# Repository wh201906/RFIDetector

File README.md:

# RFIDetector
An opensource hardware project for detecting reader field type(HF/LF)

## Copyright and License
Copyright (c) 2024 wh201906  

All hardware projects in this repository are licensed under [CERN-OHL-S v2](LICENSE.CERN-OHL-S) or any later version.

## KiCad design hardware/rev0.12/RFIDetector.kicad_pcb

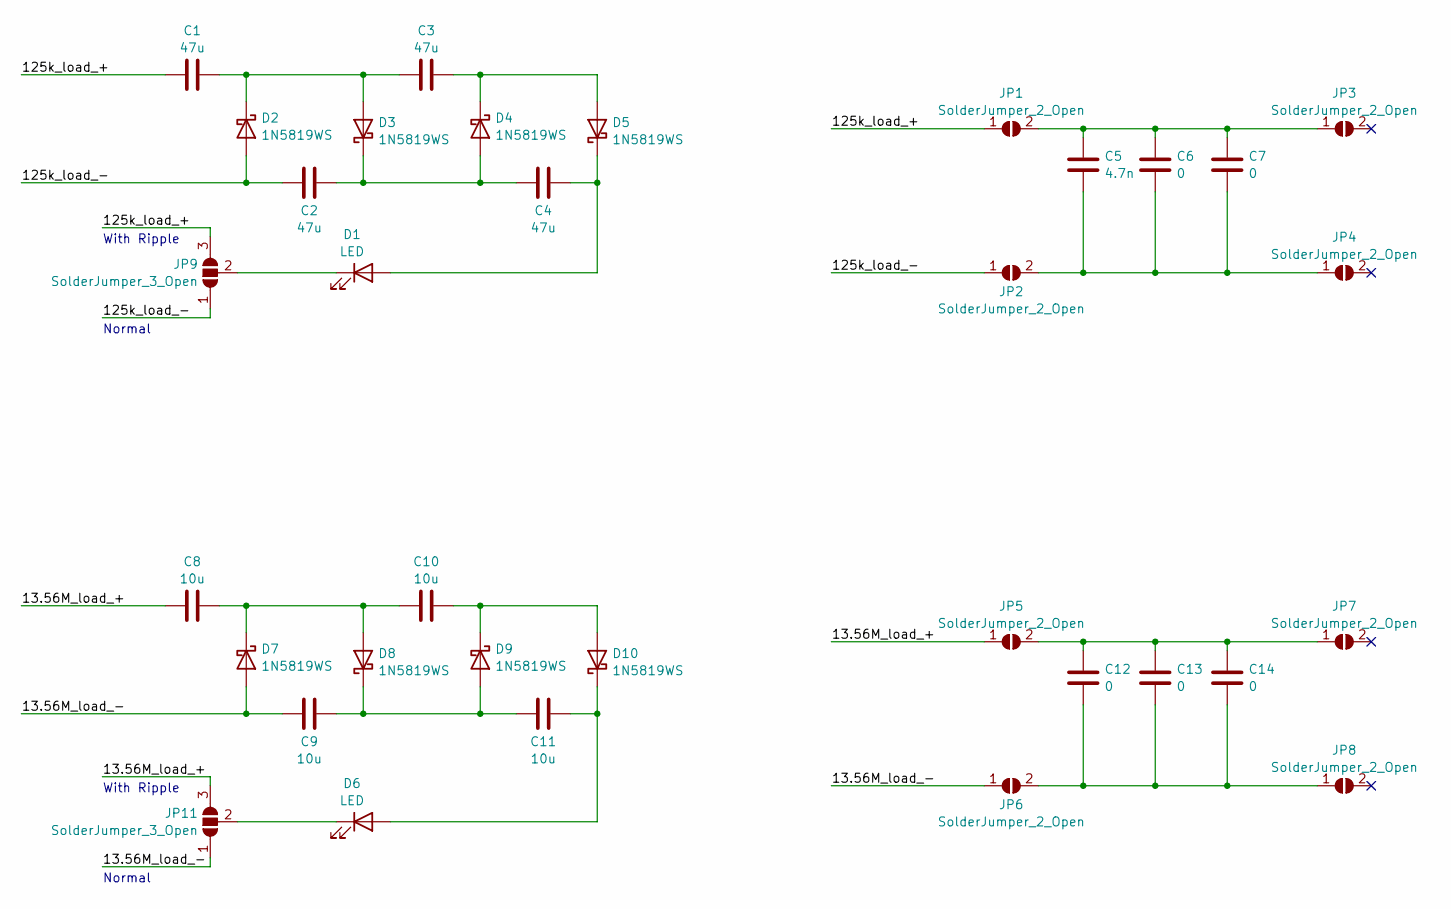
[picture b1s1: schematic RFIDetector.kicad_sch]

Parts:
C1, C2, C3, C4: 47u; C_0603_1608Metric_Pad1.08x0.95mm_HandSolder
C5: 4.7n; C_0603_1608Metric_Pad1.08x0.95mm_HandSolder
C6, C7, C12, C13, C14: 0; C_0603_1608Metric_Pad1.08x0.95mm_HandSolder
C8, C9, C10, C11: 10u; C_0603_1608Metric_Pad1.08x0.95mm_HandSolder
D1, D6: LED; LED_0603_1608Metric_Pad1.05x0.95mm_HandSolder
D2, D3, D4, D5, D7, D8, D9, D10: 1N5819WS; D_SOD-323_HandSoldering
JP1, JP2, JP3, JP4, JP5, JP6, JP7, JP8: SolderJumper_2_Open; SolderJumper-2_P1.3mm_Open_RoundedPad1.0x1.5mm
JP9, JP11: SolderJumper_3_Open; SolderJumper-3_P1.3mm_Open_RoundedPad1.0x1.5mm

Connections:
/13.56M_load_+: C8.1, JP5.1 (A), JP11.3 (B)
/13.56M_load_-: C9.1, D7.2 (A), JP6.1 (A), JP11.1 (A)
/125k_load_+: C1.1, JP1.1 (A), JP9.3 (B)
/125k_load_-: C2.1, D2.2 (A), JP2.1 (A), JP9.1 (A)
unnamed: C4.2, D1.2 (A), D5.1 (K)
unnamed: D1.1 (K), JP9.2 (C)
unnamed: C1.2, C3.1, D2.1 (K), D3.2 (A)
unnamed: C2.2, C4.1, D3.1 (K), D4.2 (A)
unnamed: C3.2, D4.1 (K), D5.2 (A)
unnamed: D6.1 (K), JP11.2 (C)
unnamed: C8.2, C10.1, D7.1 (K), D8.2 (A)
unnamed: C9.2, C11.1, D8.1 (K), D9.2 (A)
unnamed: C10.2, D9.1 (K), D10.2 (A)
unnamed: C11.2, D6.2 (A), D10.1 (K)
unnamed: C5.2, C6.2, C7.2, JP1.2 (B), JP3.1 (A)
unnamed: C5.1, C6.1, C7.1, JP2.2 (B), JP4.1 (A)
unnamed: C12.1, C13.1, C14.1, JP5.2 (B), JP7.1 (A)
unnamed: C12.2, C13.2, C14.2, JP6.2 (B), JP8.1 (A)

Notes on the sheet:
Normal
With Ripple

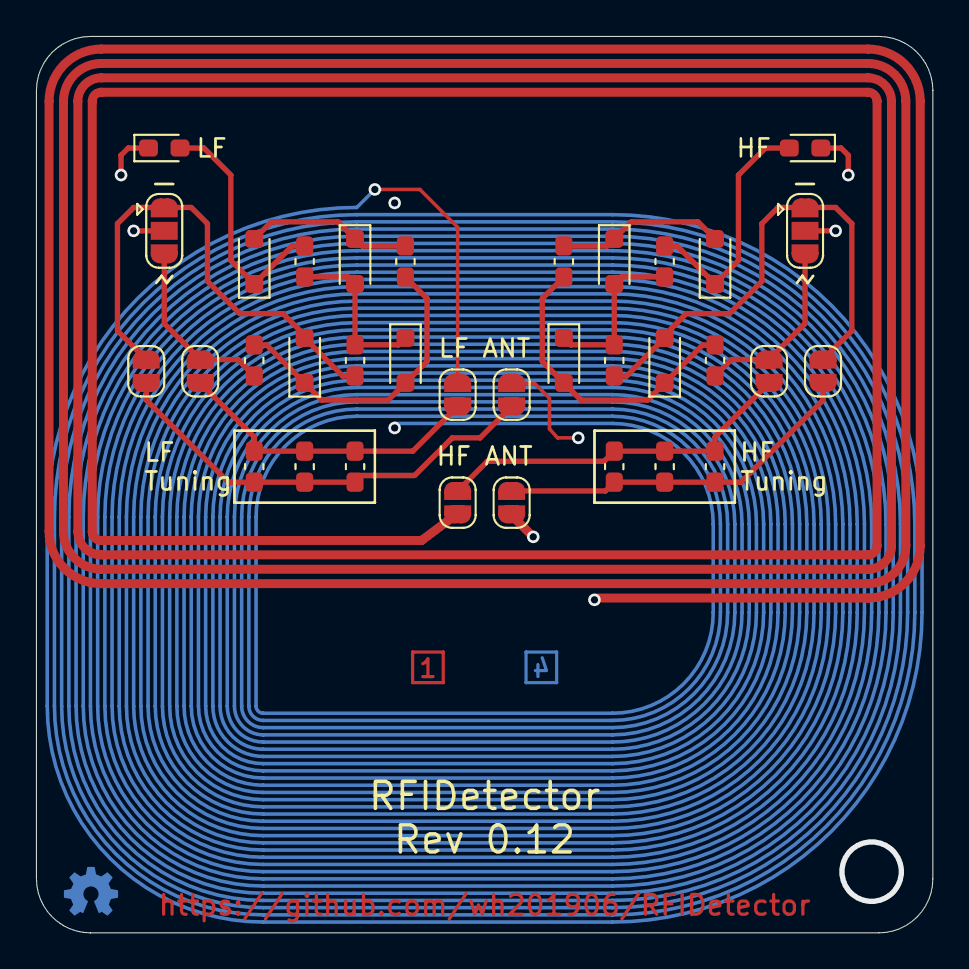
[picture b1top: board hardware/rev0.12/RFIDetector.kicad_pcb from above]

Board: 4 copper layers, 49.8 x 49.8 mm, 34 parts (0 on the bottom side), 18 nets.

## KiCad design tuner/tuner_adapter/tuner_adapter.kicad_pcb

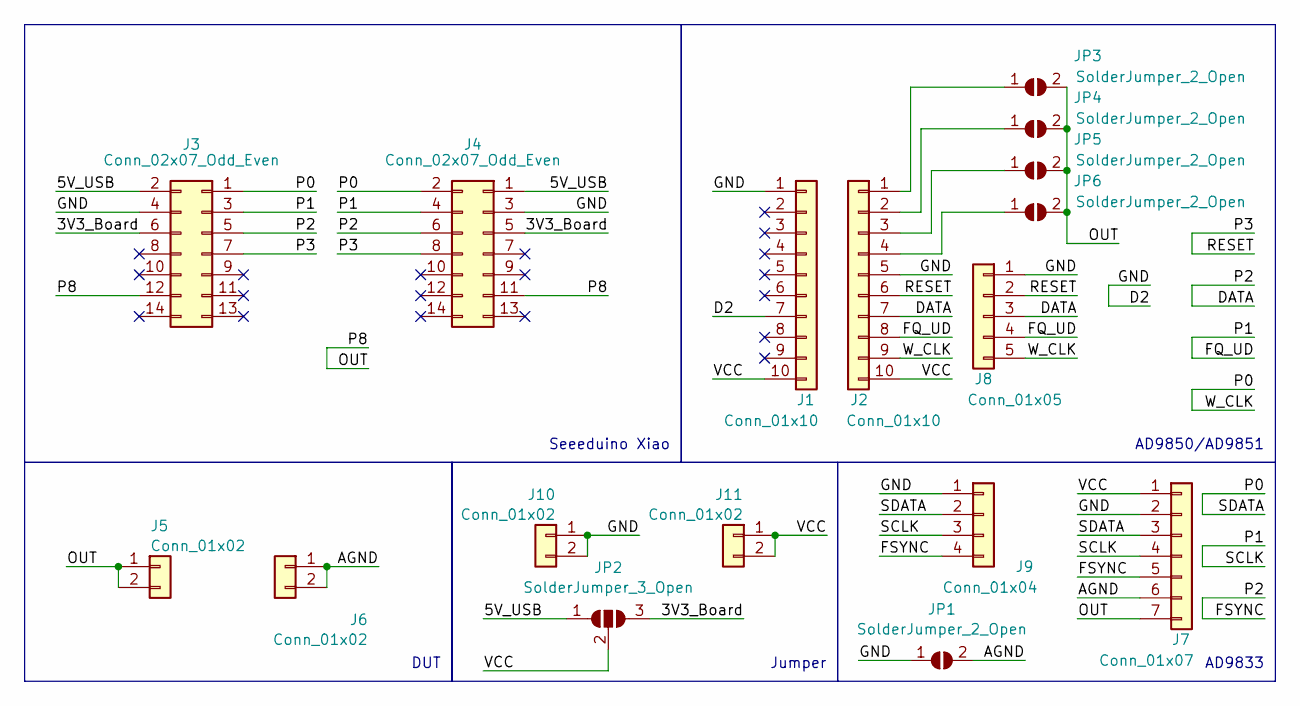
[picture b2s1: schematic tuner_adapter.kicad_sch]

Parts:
J1, J2: Conn_01x10; PinSocket_1x10_P2.54mm_Vertical
J3, J4: Conn_02x07_Odd_Even; PinSocket_2x07_P2.54mm_Vertical
J5, J6: Conn_01x02; PinSocket_1x02_P2.54mm_Vertical
J7: Conn_01x07; PinSocket_1x07_P2.54mm_Vertical
J8: Conn_01x05; PinHeader_1x05_P2.54mm_Vertical
J9: Conn_01x04; PinHeader_1x04_P2.54mm_Vertical
J10, J11: Conn_01x02; PinHeader_1x02_P2.54mm_Vertical
JP1, JP3, JP4, JP5, JP6: SolderJumper_2_Open; SolderJumper-2_P1.3mm_Open_RoundedPad1.0x1.5mm
JP2: SolderJumper_3_Open; SolderJumper-3_P1.3mm_Open_RoundedPad1.0x1.5mm

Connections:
/3V3_Board: J3.6, J4.5, JP2.3 (B)
/5V_USB: J3.2, J4.1, JP2.1 (A)
/AGND: J6.1, J6.2, J7.6, JP1.2 (B)
/D2: J1.1, J1.7, J2.5, J3.4, J4.3, J7.2, J8.1, J9.1, J10.1, J10.2, JP1.1 (A)
/DATA: J2.7, J3.5, J4.6, J7.5, J8.3, J9.4
/FQ_UD: J2.8, J3.3, J4.4, J7.4, J8.4, J9.3
/OUT: J3.12, J4.11, J5.1, J5.2, J7.7, JP3.2 (B), JP4.2 (B), JP5.2 (B), JP6.2 (B)
/P0: J2.9, J3.1, J4.2, J7.3, J8.5, J9.2
/P3: J2.6, J3.7, J4.8, J8.2
/VCC: J1.10, J2.10, J7.1, J11.1, J11.2, JP2.2 (C)
unnamed: J2.1, JP3.1 (A)
unnamed: J2.2, JP4.1 (A)
unnamed: J2.3, JP5.1 (A)
unnamed: J2.4, JP6.1 (A)

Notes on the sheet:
Jumper
AD9833
AD9850/AD9851
DUT
Seeeduino Xiao

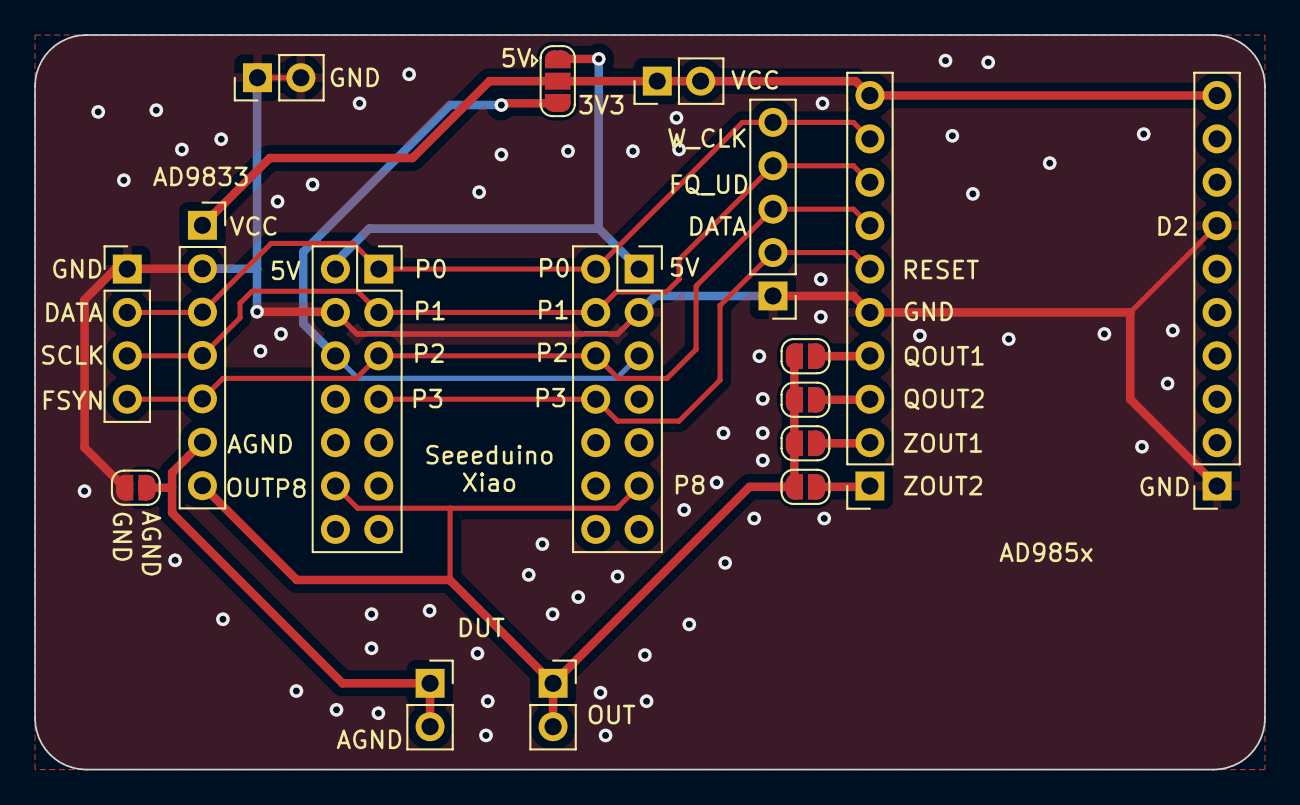
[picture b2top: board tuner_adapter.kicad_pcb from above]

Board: 2 copper layers, 72.0 x 43.0 mm, 17 parts (0 on the bottom side), 14 nets.

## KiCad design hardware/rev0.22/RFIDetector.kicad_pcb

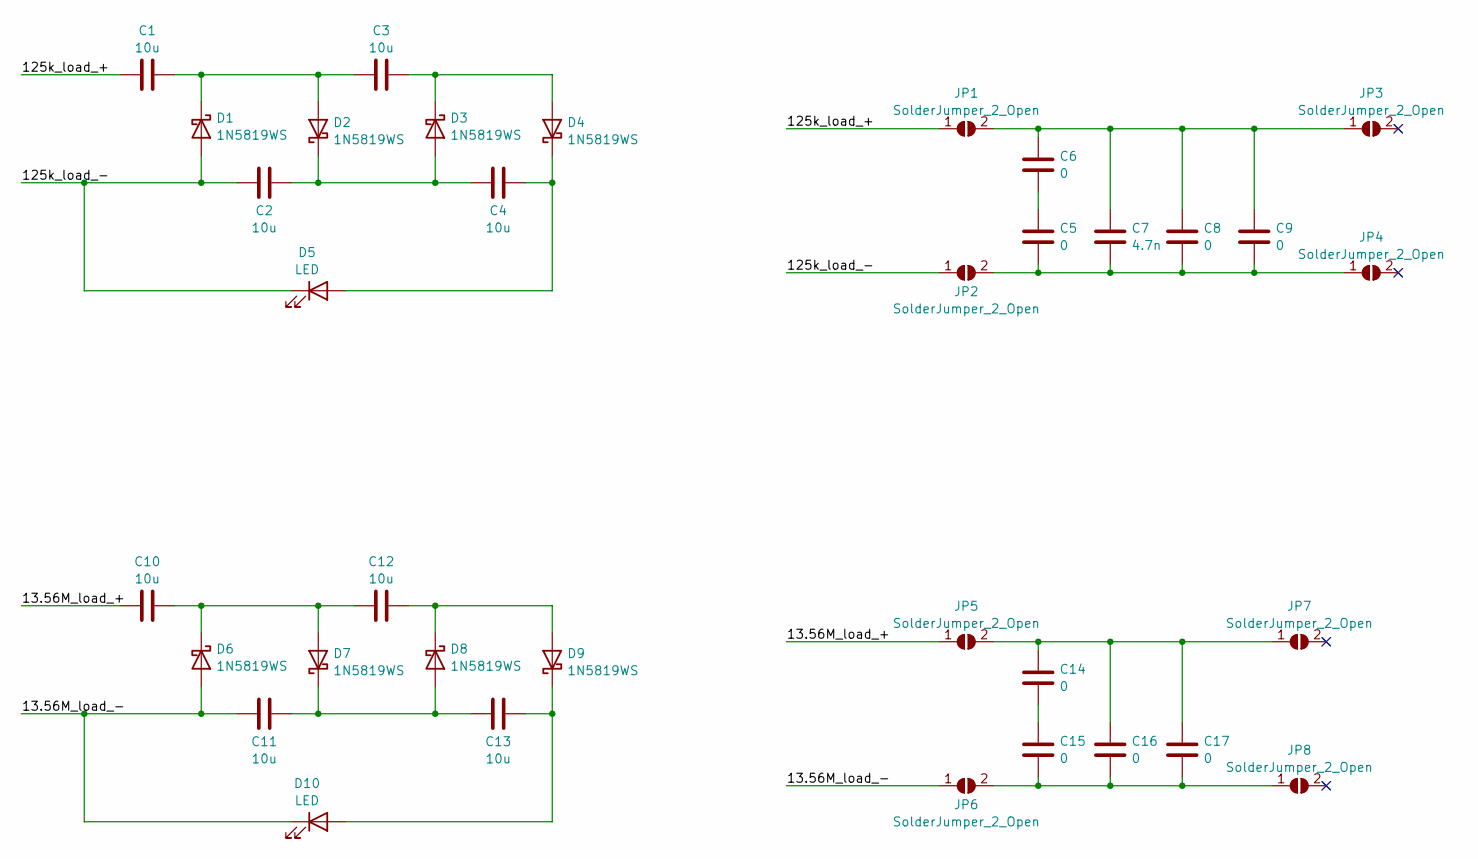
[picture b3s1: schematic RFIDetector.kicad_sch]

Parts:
C1, C2, C3, C4, C10, C11, C12, C13: 10u; C_0603_1608Metric_Pad1.08x0.95mm_HandSolder
C5, C6, C8, C9, C14, C15, C16, C17: 0; C_0603_1608Metric_Pad1.08x0.95mm_HandSolder
C7: 4.7n; C_0603_1608Metric_Pad1.08x0.95mm_HandSolder
D1, D2, D3, D4, D6, D7, D8, D9: 1N5819WS; D_SOD-323_HandSoldering
D5, D10: LED; LED_0603_1608Metric_Pad1.05x0.95mm_HandSolder
JP1, JP2, JP3, JP4, JP5, JP6, JP7, JP8: SolderJumper_2_Open; SolderJumper-2_P1.3mm_Open_RoundedPad1.0x1.5mm

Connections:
/13.56M_load_+: C10.1, JP5.1 (A)
/13.56M_load_-: C11.1, D6.2 (A), D10.1 (K), JP6.1 (A)
/125k_load_+: C1.1, JP1.1 (A)
/125k_load_-: C2.1, D1.2 (A), D5.1 (K), JP2.1 (A)
unnamed: C5.2, C6.1
unnamed: C14.1, C15.1
unnamed: C1.2, C3.1, D1.1 (K), D2.2 (A)
unnamed: C2.2, C4.1, D2.1 (K), D3.2 (A)
unnamed: C3.2, D3.1 (K), D4.2 (A)
unnamed: C4.2, D4.1 (K), D5.2 (A)
unnamed: C10.2, C12.1, D6.1 (K), D7.2 (A)
unnamed: C11.2, C13.1, D7.1 (K), D8.2 (A)
unnamed: C12.2, D8.1 (K), D9.2 (A)
unnamed: C13.2, D9.1 (K), D10.2 (A)
unnamed: C6.2, C7.1, C8.1, C9.1, JP1.2 (B), JP3.1 (A)
unnamed: C5.1, C7.2, C8.2, C9.2, JP2.2 (B), JP4.1 (A)
unnamed: C14.2, C16.2, C17.2, JP5.2 (B), JP7.1 (A)
unnamed: C15.2, C16.1, C17.1, JP6.2 (B), JP8.1 (A)

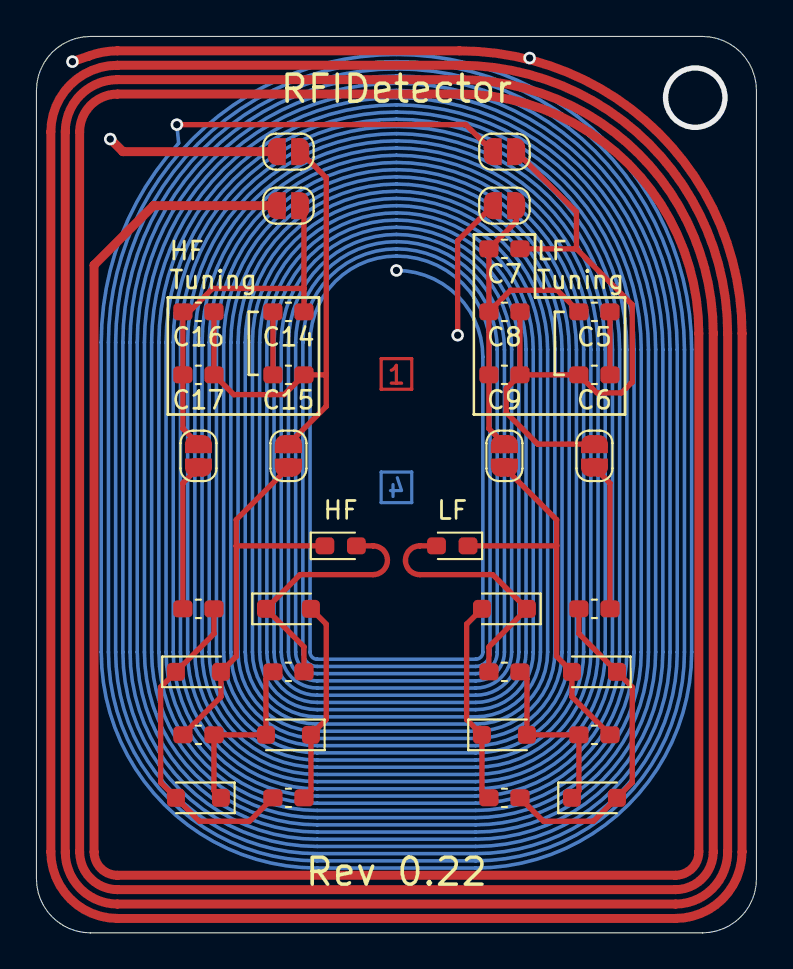
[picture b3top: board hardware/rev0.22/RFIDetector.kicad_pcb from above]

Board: 4 copper layers, 40.0 x 49.8 mm, 35 parts (0 on the bottom side), 18 nets.

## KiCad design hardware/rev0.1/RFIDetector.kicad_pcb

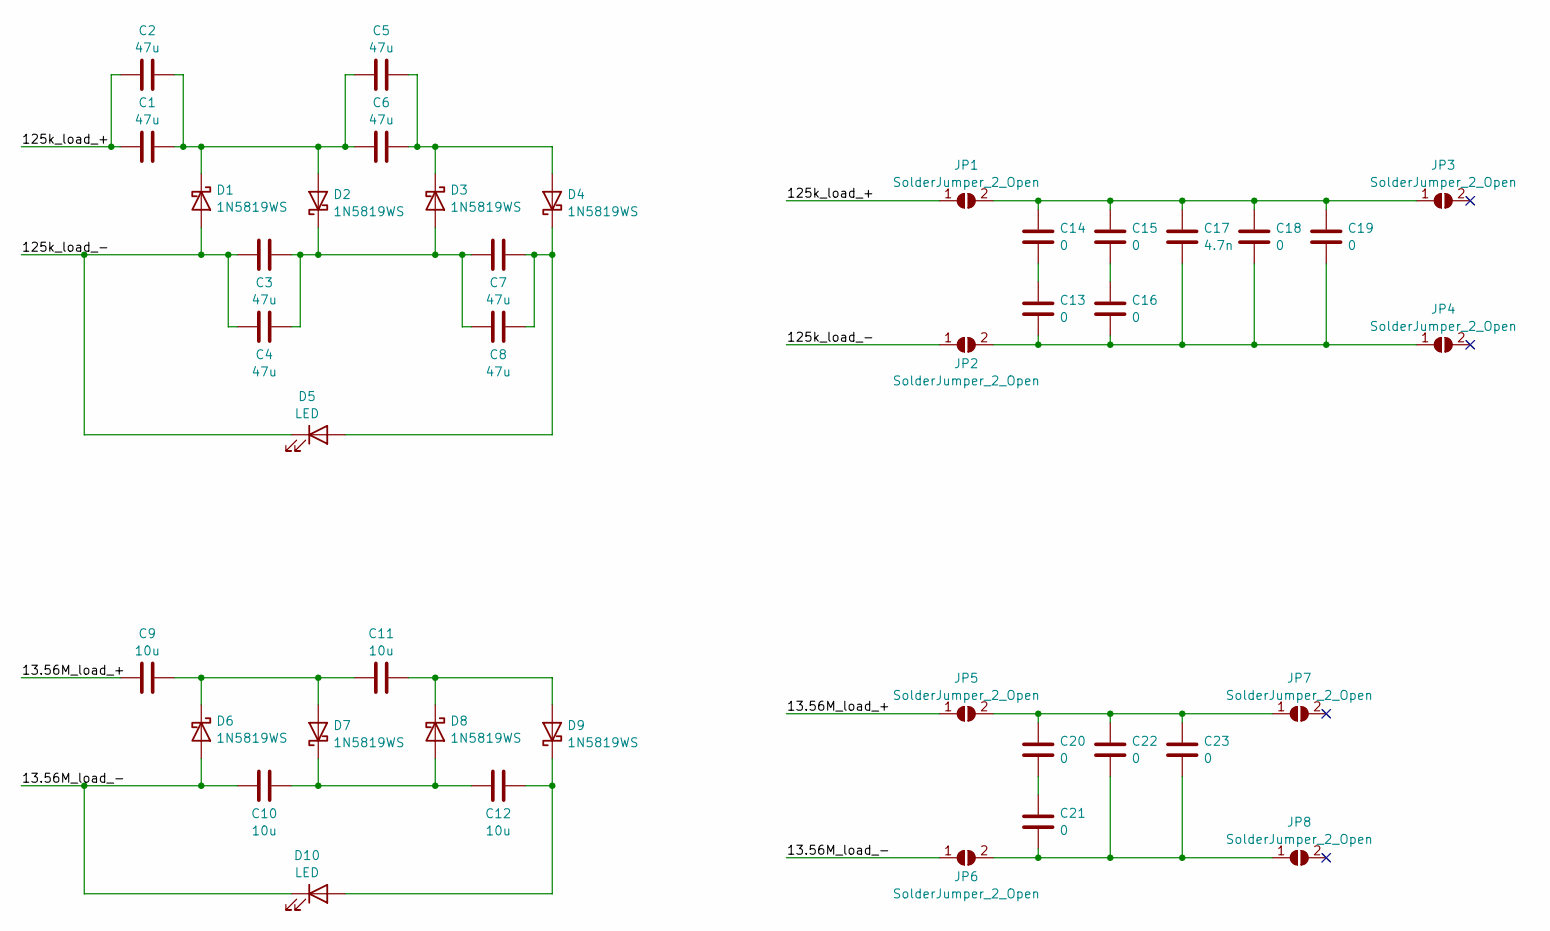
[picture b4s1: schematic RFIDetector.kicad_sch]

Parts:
C1, C2, C3, C4, C5, C6, C7, C8: 47u; C_0603_1608Metric_Pad1.08x0.95mm_HandSolder
C9, C10, C11, C12: 10u; C_0603_1608Metric_Pad1.08x0.95mm_HandSolder
C13, C14, C15, C16, C18, C19, C20, C21, C22, C23: 0; C_0603_1608Metric_Pad1.08x0.95mm_HandSolder
C17: 4.7n; C_0603_1608Metric_Pad1.08x0.95mm_HandSolder
D1, D2, D3, D4, D6, D7, D8, D9: 1N5819WS; D_SOD-323_HandSoldering
D5, D10: LED; LED_0603_1608Metric_Pad1.05x0.95mm_HandSolder
JP1, JP2, JP3, JP4, JP5, JP6, JP7, JP8: SolderJumper_2_Open; SolderJumper-2_P1.3mm_Open_RoundedPad1.0x1.5mm

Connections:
/13.56M_load_+: C9.1, JP5.1 (A)
/13.56M_load_-: C10.1, D6.2 (A), D10.1 (K), JP6.1 (A)
/125k_load_+: C1.1, C2.1, JP1.1 (A)
/125k_load_-: C3.1, C4.1, D1.2 (A), D5.1 (K), JP2.1 (A)
unnamed: C13.1, C14.1
unnamed: C15.2, C16.1
unnamed: C20.1, C21.1
unnamed: C1.2, C2.2, C5.1, C6.1, D1.1 (K), D2.2 (A)
unnamed: C3.2, C4.2, C7.1, C8.1, D2.1 (K), D3.2 (A)
unnamed: C5.2, C6.2, D3.1 (K), D4.2 (A)
unnamed: C7.2, C8.2, D4.1 (K), D5.2 (A)
unnamed: C9.2, C11.1, D6.1 (K), D7.2 (A)
unnamed: C10.2, C12.1, D7.1 (K), D8.2 (A)
unnamed: C11.2, D8.1 (K), D9.2 (A)
unnamed: C12.2, D9.1 (K), D10.2 (A)
unnamed: C14.2, C15.1, C17.2, C18.2, C19.2, JP1.2 (B), JP3.1 (A)
unnamed: C13.2, C16.2, C17.1, C18.1, C19.1, JP2.2 (B), JP4.1 (A)
unnamed: C20.2, C22.1, C23.1, JP5.2 (B), JP7.1 (A)
unnamed: C21.2, C22.2, C23.2, JP6.2 (B), JP8.1 (A)

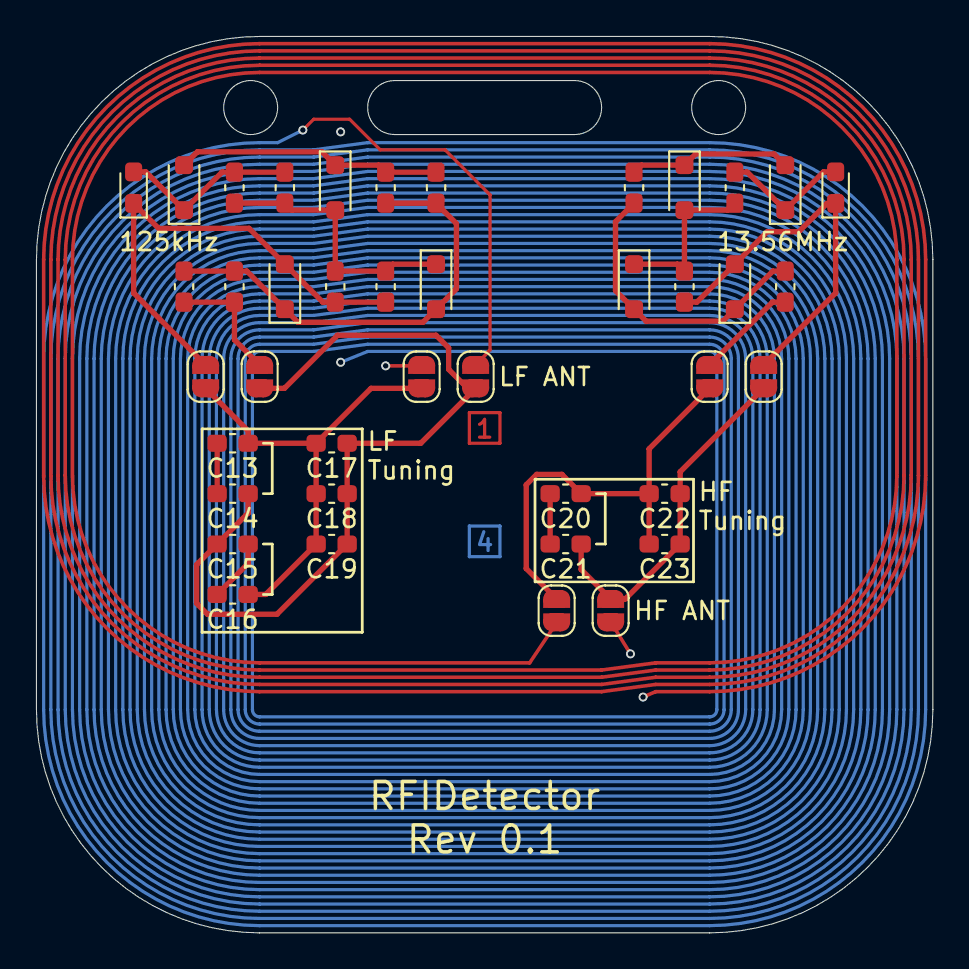
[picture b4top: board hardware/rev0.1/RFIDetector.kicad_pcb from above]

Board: 4 copper layers, 49.8 x 49.8 mm, 41 parts (0 on the bottom side), 19 nets.

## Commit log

2024-01-12 Rev 0.1, untested, untuned
2024-01-28 Rev 0.1
2024-01-29 Rev 0.2, untested, untuned
    Set the board size to 49.8mm x 40.0mm
    Set the trace width of LF antenna to 0.2mm
    Set the trace width of HF antenna to 0.5mm
    Set the spacing of HF antenna to 0.3mm
    Set the via size to 0.4mm/0.7mm
    Removed some holes
2024-01-29 Rev 0.21, untested, untuned
    Reduced the number of turns of HF antenna(5->4) for lower inductance
    Hide the jumper wire of HF antenna into the inner layer
2024-02-03 Add tuner script and some tuning result of Rev 0.1
    Just a prototype
2024-02-19 Add tuner firmware(AD9851)
2024-02-20 Rev 0.22, untested, untuned
    Decreased the size of LF antenna to reduce the overlapped part
    Flipped the "3" and "4" mark
2024-02-23 Rev 0.11, untested, untuned
    Apply some changes from Rev 0.2x, but keep the size and coil layout
    unchanged
2024-02-29 Add tuner adapter project
    Less jump wires and much less noise on ADC
2024-03-01 Add test results
    The signal is from AD9851
2024-03-07 Add test results
2024-03-22 Rev 0.12, untested, untuned
    Set the spacing of HF antenna to 0.3mm
    Align some components
    Decrease the size of the coils
    Make more gaps around the coils
    Add silkscreens to indicate normal/jitter mode
    This revision is based on Rev 0.11, but saved as KiCad 8 project.
